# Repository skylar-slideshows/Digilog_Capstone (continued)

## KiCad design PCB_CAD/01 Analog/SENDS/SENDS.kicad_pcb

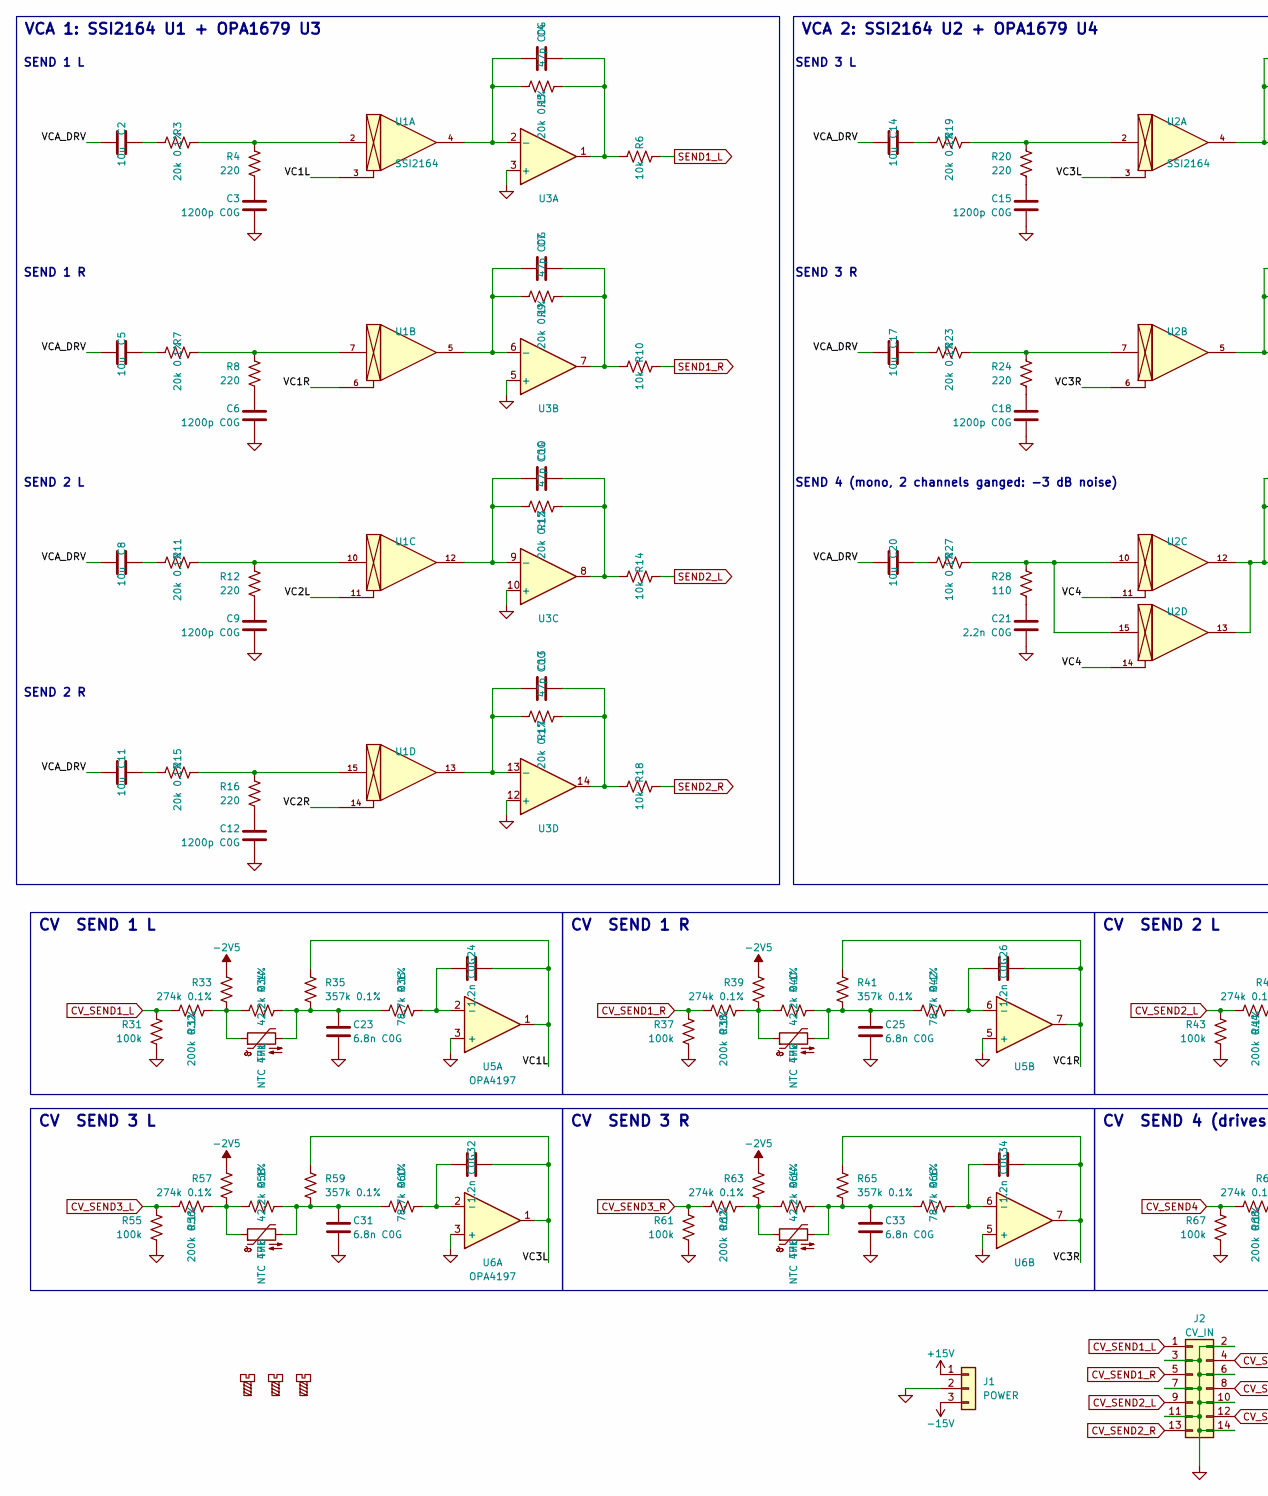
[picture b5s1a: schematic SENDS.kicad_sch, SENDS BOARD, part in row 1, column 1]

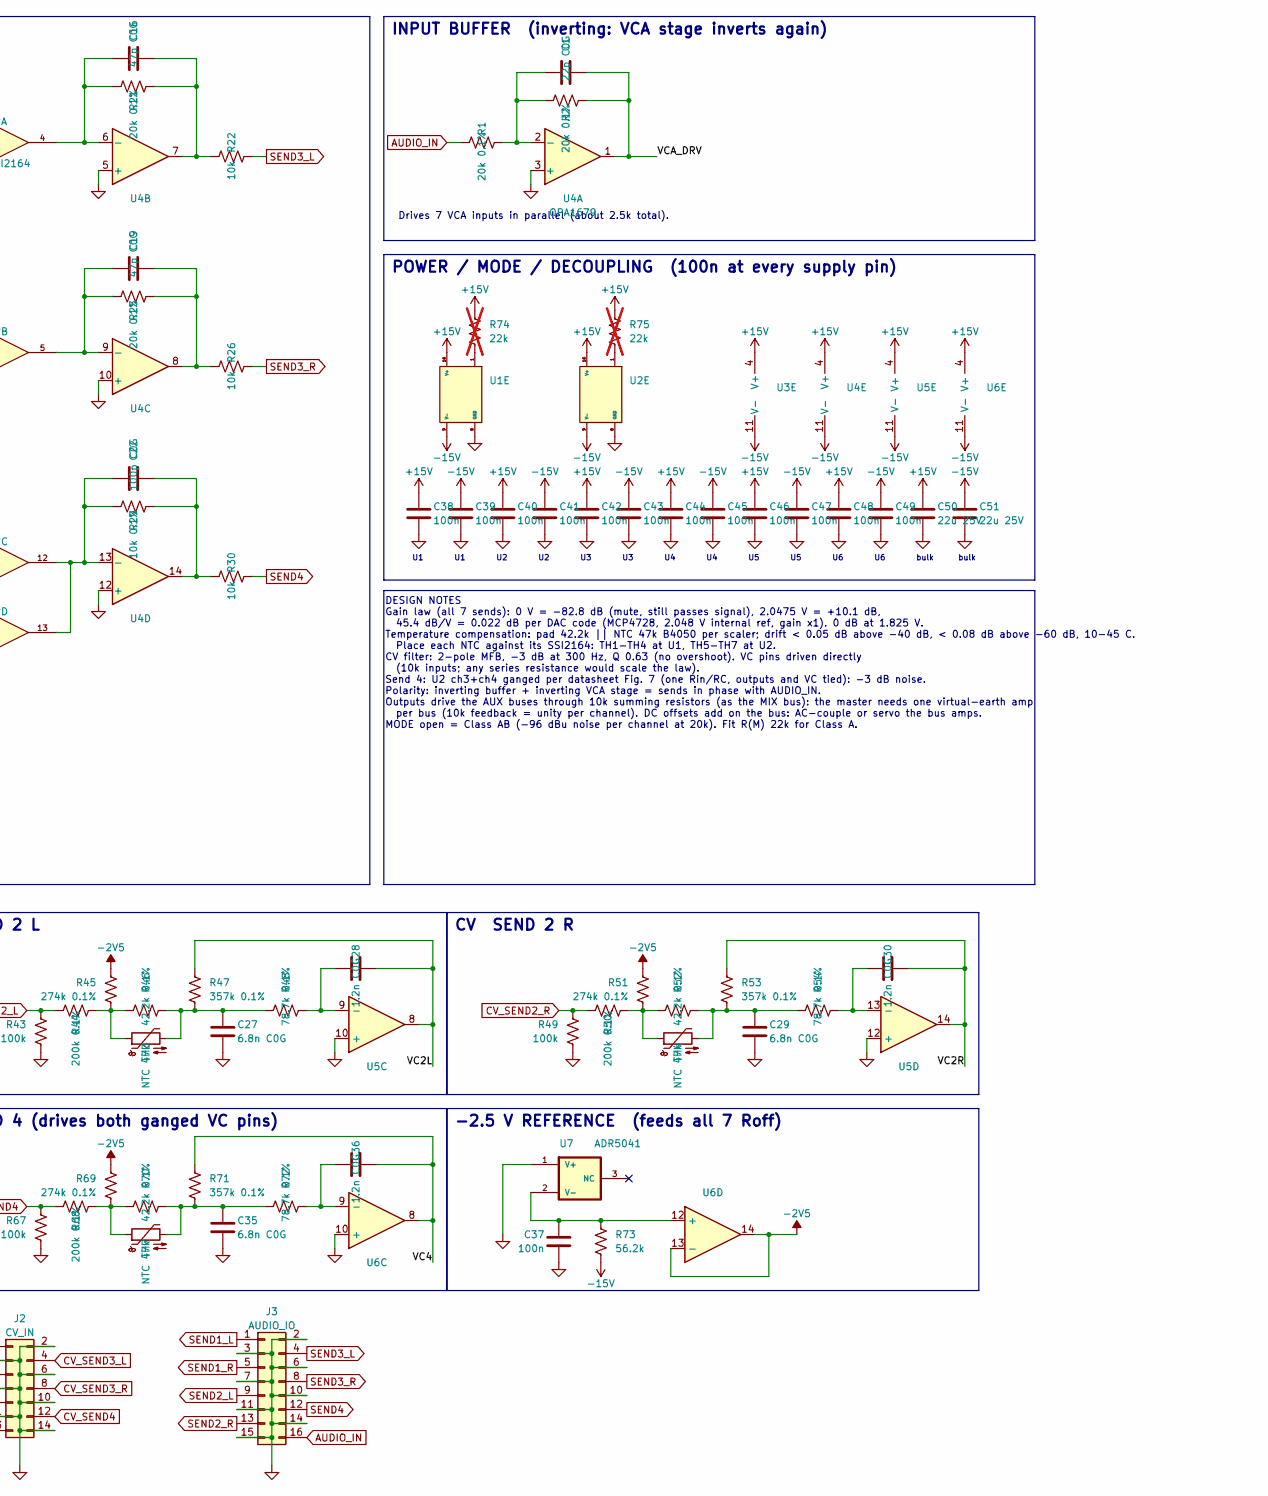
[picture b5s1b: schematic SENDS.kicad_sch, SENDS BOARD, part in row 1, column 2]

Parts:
C1: 22p C0G; C_0603_1608Metric; LCSC C105620
C2, C5, C8, C11, C14, C17, C20: 10u; CP_Elec_6.3x5.4_Nichicon; LCSC C192559
C3, C6, C9, C12, C15, C18: 1200p C0G; C_0603_1608Metric; LCSC C576796
C4, C7, C10, C13, C16, C19: 47p C0G; C_0603_1608Metric; LCSC C105622
C21: 2.2n C0G; C_0603_1608Metric; LCSC C107043
C22: 100p C0G; C_0603_1608Metric; LCSC C14665
C23, C25, C27, C29, C31, C33, C35: 6.8n C0G; C_0603_1608Metric; LCSC C513559
C24, C26, C28, C30, C32, C34, C36: 1.2n C0G; C_0603_1608Metric; LCSC C576796
C37, C38, C39, C40, C41, C42, C43, C44, C45, C46, C47, C48, C49: 100n; C_0603_1608Metric; LCSC C1590
C50, C51: 22u 25V; C_1210_3225Metric; LCSC C21397
H1, H2, H3: MountingScrew; MountingHole_2.2mm_M2; LCSC dnp
J1: POWER; PinHeader_1x03_P2.54mm_Vertical; LCSC dnp
J2: CV_IN; PinHeader_2x07_P2.54mm_Vertical; LCSC dnp
J3: AUDIO_IO; PinHeader_2x08_P2.54mm_Vertical; LCSC dnp
R1, R2, R3, R5, R7, R9, R11, R13, R15, R17, R19, R21, R23, R25: 20k 0.1%; R_0603_1608Metric; LCSC C190611
R4, R8, R12, R16, R20, R24: 220; R_0603_1608Metric; LCSC C217883
R6, R10, R14, R18, R22, R26, R30: 10k; R_0603_1608Metric; LCSC C95204
R27, R29: 10k 0.1%; R_0603_1608Metric; LCSC C95204
R28: 110; R_0603_1608Metric; LCSC C351689
R31, R37, R43, R49, R55, R61, R67: 100k; R_0603_1608Metric; LCSC C122538
R32, R38, R44, R50, R56, R62, R68: 200k 0.1%; R_0603_1608Metric; LCSC C136955
R33, R39, R45, R51, R57, R63, R69: 274k 0.1%; R_0603_1608Metric; LCSC C311972
R34, R40, R46, R52, R58, R64, R70: 42.2k 0.1%; R_0603_1608Metric; LCSC C861398
R35, R41, R47, R53, R59, R65, R71: 357k 0.1%; R_0603_1608Metric; LCSC C217978
R36, R42, R48, R54, R60, R66, R72: 78.7k 0.1%; R_0603_1608Metric; LCSC C861558
R73: 56.2k; R_0603_1608Metric; LCSC C23080
R74, R75: 22k; R_0603_1608Metric; LCSC C23344; not fitted
TH1, TH2, TH3, TH4, TH5, TH6, TH7: NTC 47k; R_Axial_DIN0207_L6.3mm_D2.5mm_P2.54mm_Vertical; LCSC dnp
U1, U2: SSI2164; SSI2164_breakout; LCSC dnp
U3, U4: OPA1679; TSSOP-14_4.4x5mm_P0.65mm; LCSC C2057264
U5, U6: OPA4197; SOIC-14_3.9x8.7mm_P1.27mm; LCSC C2058532
U7: ADR5041; SOT-23; LCSC C2686108

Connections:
+15V: C38.1, C40.1, C42.1, C44.1, C46.1, C48.1, C50.1, J1.1, R74.1, R75.1, U1.16 (V+), U2.16 (V+), U3.4 (V+), U4.4 (V+), U5.4 (V+), U6.4 (V+)
-2V5: R33.1, R39.1, R45.1, R51.1, R57.1, R63.1, R69.1, U6.13 (-), U6.14
-15V: C39.1, C41.1, C43.1, C45.1, C47.1, C49.1, C51.1, J1.3, R73.2, U1.9 (V-), U2.9 (V-), U3.11 (V-), U4.11 (V-), U5.11 (V-), U6.11 (V-)
/VC1L: C24.2, R35.1, U1.3, U5.1
/VC1R: C26.2, R41.1, U1.6, U5.7
/VC2L: C28.2, R47.1, U1.11, U5.8
/VC2R: C30.2, R53.1, U1.14, U5.14
/VC3L: C32.2, R59.1, U2.3, U6.1
/VC3R: C34.2, R65.1, U2.6, U6.7
/VC4: C36.2, R71.1, U2.11, U2.14, U6.8
/VCA_DRV: C1.2, C2.1, C5.1, C8.1, C11.1, C14.1, C17.1, C20.1, R2.2, U4.1
AUDIO_IN: J3.16, R1.1
CV_SEND1_L: J2.1, R31.1, R32.1
CV_SEND1_R: J2.5, R37.1, R38.1
CV_SEND2_L: J2.9, R43.1, R44.1
CV_SEND2_R: J2.13, R49.1, R50.1
CV_SEND3_L: J2.4, R55.1, R56.1
CV_SEND3_R: J2.8, R61.1, R62.1
CV_SEND4: J2.12, R67.1, R68.1
GND: C3.2, C6.2, C9.2, C12.2, C15.2, C18.2, C21.2, C23.2, C25.2, C27.2, C29.2, C31.2, C33.2, C35.2, C37.2, C38.2, C39.2, C40.2, C41.2, C42.2, C43.2, C44.2, C45.2, C46.2, C47.2, C48.2, C49.2, C50.2, C51.2, J1.2, J2.2, J2.3, J2.6, J2.7, J2.10, J2.11, J2.14, J3.2, J3.3, J3.6, J3.7, J3.10, J3.11, J3.14, J3.15, R31.2, R37.2, R43.2, R49.2, R55.2, R61.2, R67.2, U1.8 (GND), U2.8 (GND), U3.3 (+), U3.5 (+), U3.10 (+), U3.12 (+), U4.3 (+), U4.5 (+), U4.10 (+), U4.12 (+), U5.3 (+), U5.5 (+), U5.10 (+), U5.12 (+), U6.3 (+), U6.5 (+), U6.10 (+), U7.1 (V+)
unnamed: C2.2, R3.1
unnamed: C3.1, R4.2
unnamed: C4.2, R5.2, R6.1, U3.1
unnamed: C5.2, R7.1
unnamed: C6.1, R8.2
unnamed: C7.2, R9.2, R10.1, U3.7
unnamed: C8.2, R11.1
unnamed: C9.1, R12.2
unnamed: C10.2, R13.2, R14.1, U3.8
unnamed: C11.2, R15.1
unnamed: C12.1, R16.2
unnamed: C13.2, R17.2, R18.1, U3.14
unnamed: C14.2, R19.1
unnamed: C15.1, R20.2
unnamed: C16.2, R21.2, R22.1, U4.7
unnamed: C17.2, R23.1
unnamed: C18.1, R24.2
unnamed: C19.2, R25.2, R26.1, U4.8
unnamed: C20.2, R27.1
unnamed: C21.1, R28.2
unnamed: C22.2, R29.2, R30.1, U4.14
unnamed: C23.1, R34.2, R35.2, R36.1, TH1.2
unnamed: C25.1, R40.2, R41.2, R42.1, TH2.2
unnamed: C27.1, R46.2, R47.2, R48.1, TH3.2
unnamed: C29.1, R52.2, R53.2, R54.1, TH4.2
unnamed: C31.1, R58.2, R59.2, R60.1, TH5.2
unnamed: C33.1, R64.2, R65.2, R66.1, TH6.2
unnamed: C35.1, R70.2, R71.2, R72.1, TH7.2
unnamed: R3.2, R4.1, U1.2
unnamed: R7.2, R8.1, U1.7
unnamed: R11.2, R12.1, U1.10
unnamed: R15.2, R16.1, U1.15
unnamed: R19.2, R20.1, U2.2
unnamed: R23.2, R24.1, U2.7
unnamed: R27.2, R28.1, U2.10, U2.15
unnamed: R32.2, R33.2, R34.1, TH1.1
unnamed: R38.2, R39.2, R40.1, TH2.1
unnamed: R44.2, R45.2, R46.1, TH3.1
unnamed: R50.2, R51.2, R52.1, TH4.1
unnamed: R56.2, R57.2, R58.1, TH5.1
unnamed: R62.2, R63.2, R64.1, TH6.1
unnamed: R68.2, R69.2, R70.1, TH7.1
unnamed: R74.2, U1.1
unnamed: R75.2, U2.1
unnamed: C4.1, R5.1, U1.4, U3.2 (-)
unnamed: C7.1, R9.1, U1.5, U3.6 (-)
unnamed: C10.1, R13.1, U1.12, U3.9 (-)
unnamed: C13.1, R17.1, U1.13, U3.13 (-)
unnamed: C1.1, R1.2, R2.1, U4.2 (-)
unnamed: C16.1, R21.1, U2.4, U4.6 (-)
unnamed: C19.1, R25.1, U2.5, U4.9 (-)
unnamed: C22.1, R29.1, U2.12, U2.13, U4.13 (-)
unnamed: C24.1, R36.2, U5.2 (-)
unnamed: C26.1, R42.2, U5.6 (-)
unnamed: C28.1, R48.2, U5.9 (-)
unnamed: C30.1, R54.2, U5.13 (-)
unnamed: C32.1, R60.2, U6.2 (-)
unnamed: C34.1, R66.2, U6.6 (-)
unnamed: C36.1, R72.2, U6.9 (-)
unnamed: C37.1, R73.1, U6.12 (+), U7.2 (V-)
SEND1_L: J3.1, R6.2
SEND1_R: J3.5, R10.2
SEND2_L: J3.9, R14.2
SEND2_R: J3.13, R18.2
SEND3_L: J3.4, R22.2
SEND3_R: J3.8, R26.2
SEND4: J3.12, R30.2

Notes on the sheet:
bulk
SEND 2 R
SEND 1 L
CV SEND 4 (drives both ganged VC pins)
SEND 1 R
DESIGN NOTES Gain law (all 7 sends): 0 V = -82.8 dB (mute, still passes signal), 2.0475 V = +10.1 dB, 45.4 dB/V = 0.022 dB per DAC code (MCP4728, 2.048 V internal ref, gain x1). 0 dB at 1.825 V. Temperature compensation: pad 42.2k || NTC 47k B4050 per scaler; drift < 0.05 dB above -40 dB, < 0.08 dB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
VCA 1: SSI2164 U1 + OPA1679 U3
CV SEND 1 R
Drives 7 VCA inputs in parallel (about 2.5k total).
-2.5 V REFERENCE (feeds all 7 Roff)
CV SEND 3 R
VCA 2: SSI2164 U2 + OPA1679 U4
SEND 4 (mono, 2 channels ganged: -3 dB noise)
SEND 2 L
CV SEND 1 L
SEND 3 L
CV SEND 2 L
INPUT BUFFER (inverting: VCA stage inverts again)
CV SEND 2 R
SEND 3 R
POWER / MODE / DECOUPLING (100n at every supply pin)
CV SEND 3 L

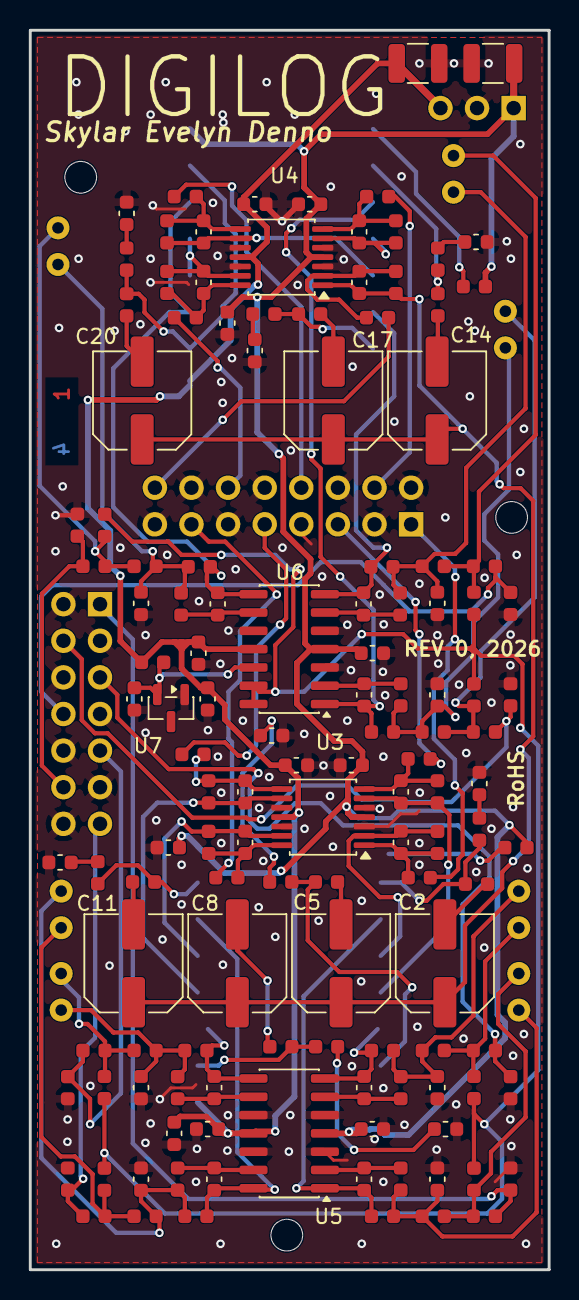
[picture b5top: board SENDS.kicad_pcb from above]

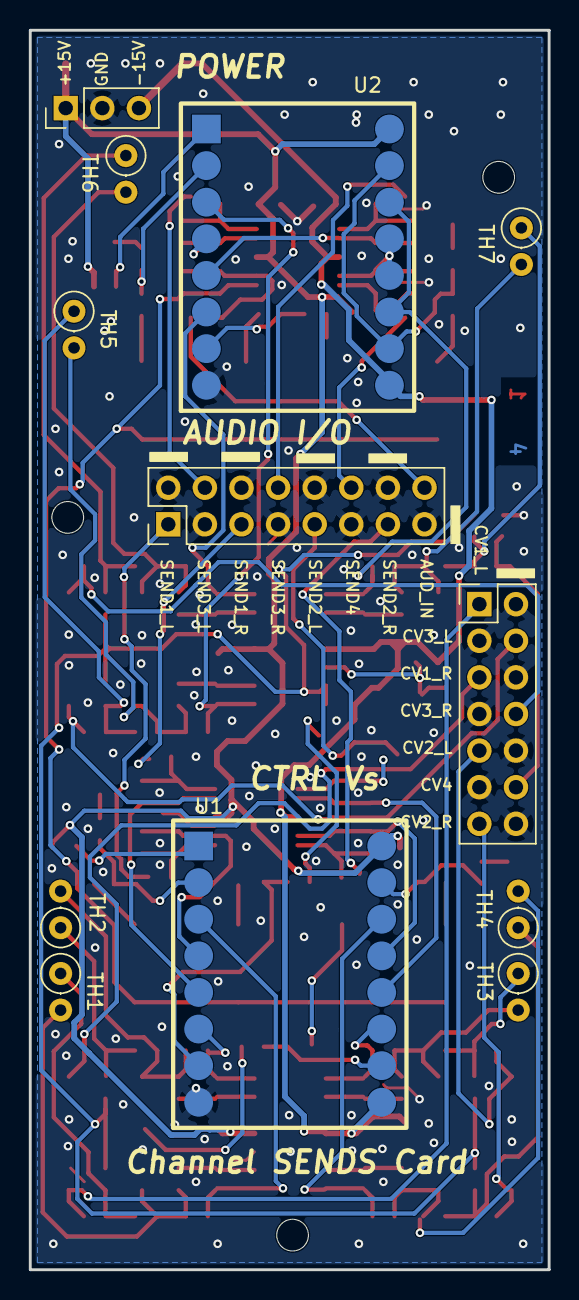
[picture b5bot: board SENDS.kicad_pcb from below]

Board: 4 copper layers, 36.0 x 86.0 mm, 146 parts (12 on the bottom side), 87 nets.

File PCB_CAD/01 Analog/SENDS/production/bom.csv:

Designator,Footprint,Quantity,Value,LCSC Part #
C1,0603,1,22p C0G,C105620
"C10, C13, C16, C19, C4, C7",0603,6,47p C0G,C105622
"C11, C14, C17, C2, C20, C5, C8",CP_Elec_6.3x5.4_Nichicon,7,10u,C192559
"C12, C15, C18, C3, C6, C9",0603,6,1200p C0G,C576796
C21,0603,1,2.2n C0G,C107043
C22,0603,1,100p C0G,C14665
"C23, C25, C27, C29, C31, C33, C35",0603,7,6.8n C0G,C513559
"C24, C26, C28, C30, C32, C34, C36",0603,7,1.2n C0G,C576796
"C37, C38, C39, C40, C41, C42, C43, C44, C45, C46, C47, C48, C49",0603,13,100n,C1590
"C50, C51",1210,2,22u 25V,C21397
J1,PinHeader_1x03_P2.54mm_Vertical,1,POWER,dnp
J2,PinHeader_2x07_P2.54mm_Vertical,1,CV_IN,dnp
J3,PinHeader_2x08_P2.54mm_Vertical,1,AUDIO_IO,dnp
"R1, R11, R13, R15, R17, R19, R2, R21, R23, R25, R3, R5, R7, R9",0603,14,20k 0.1%,C190611
"R10, R14, R18, R22, R26, R30, R6",0603,7,10k,C95204
"R12, R16, R20, R24, R4, R8",0603,6,220,C217883
"R27, R29",0603,2,10k 0.1%,C95204
R28,0603,1,110,C351689
"R31, R37, R43, R49, R55, R61, R67",0603,7,100k,C122538
"R32, R38, R44, R50, R56, R62, R68",0603,7,200k 0.1%,C136955
"R33, R39, R45, R51, R57, R63, R69",0603,7,274k 0.1%,C311972
"R34, R40, R46, R52, R58, R64, R70",0603,7,42.2k 0.1%,C861398
"R35, R41, R47, R53, R59, R65, R71",0603,7,357k 0.1%,C217978
"R36, R42, R48, R54, R60, R66, R72",0603,7,78.7k 0.1%,C861558
R73,0603,1,56.2k,C23080
"R74, R75",0603,2,22k,C23344
"TH1, TH2, TH3, TH4, TH5, TH6, TH7",R_Axial_DIN0207_L6.3mm_D2.5mm_P2.54mm_Vertical,7,NTC 47k,dnp
"U1, U2",SSI2164_breakout,2,SSI2164,dnp
"U3, U4",TSSOP-14_4.4x5mm_P0.65mm,2,OPA1679,C2057264
"U5, U6",SOIC-14_3.9x8.7mm_P1.27mm,2,OPA4197,C2058532
U7,SOT-23,1,ADR5041,C2686108

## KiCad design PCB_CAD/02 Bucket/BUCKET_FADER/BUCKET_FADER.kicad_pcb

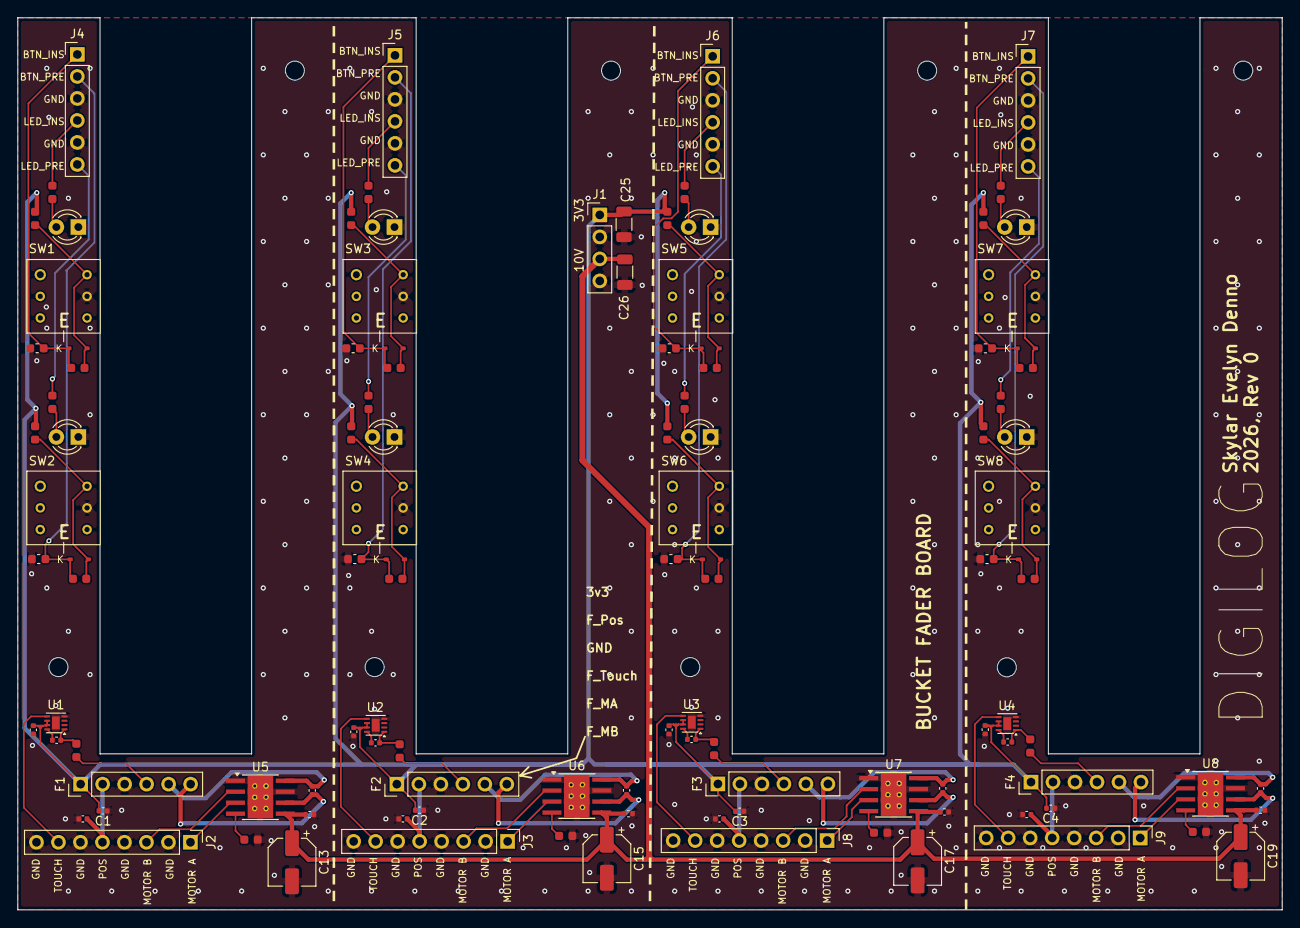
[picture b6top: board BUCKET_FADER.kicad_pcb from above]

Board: 4 copper layers, 146.0 x 103.0 mm, 123 parts (0 on the bottom side), 75 nets.

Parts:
C1, C2, C3, C4, C5, C6, C7, C8, C14, C16, C18, C20, C35, C36, C37, C38: 100n; C_0402_1005Metric
C9, C10, C11, C12, C21, C22, C23, C24: 10n; C_0402_1005Metric
C13, C15, C17, C19: 22u; CP_Elec_5x5.4
C25, C26: 10u; C_1206_3216Metric
C27, C28, C29, C30, C31, C32, C33, C34: 1u; C_0603_1608Metric
D1, D2, D3, D4, D9, D10, D11, D12: 1N4148; D_SOD-323
D5, D6, D7, D8, D13, D14, D15, D16: LED; LED_D3.0mm_FlatTop
F1, F2, F3, F4: Alps_RSA0N11M9; PinHeader_1x06_P2.54mm_Vertical
H1, H2, H3, H4, H5, H6, H7, H8: MountingScrew; MountingHole_2.2mm_M2
J1: POW; PinHeader_1x04_P2.54mm_Vertical
J2: F0_MCU; PinHeader_1x08_P2.54mm_Vertical
J3: F1_MCU; PinHeader_1x08_P2.54mm_Vertical
J4: F0_BTN; PinHeader_1x06_P2.54mm_Vertical
J5: F1_BTN; PinHeader_1x06_P2.54mm_Vertical
J6: F2_BTN; PinHeader_1x06_P2.54mm_Vertical
J7: F3_BTN; PinHeader_1x06_P2.54mm_Vertical
J8: F2_MCU; PinHeader_1x08_P2.54mm_Vertical
J9: F3_MCU; PinHeader_1x08_P2.54mm_Vertical
R1, R2, R3, R4: 10k; R_0603_1608Metric
R5, R6, R7, R8: 82k; R_0603_1608Metric
R9, R10, R11, R12, R21, R22, R23, R24: 47k; R_0603_1608Metric
R13, R14, R15, R16, R25, R26, R27, R28: 15k; R_0603_1608Metric
R17, R18, R19, R20, R29, R30, R31, R32: 6.8k; R_0603_1608Metric
SW1, SW3, SW5, SW7: C0_B10; TL2201EEZB
SW2, SW4, SW6, SW8: C0_B11; TL2201EEZB
U1, U2, U3, U4: AT42QT1011-M; DFN-8-1EP_2x2mm_P0.5mm_EP0.9x1.5mm
U5, U6, U7, U8: DRV8871DDA; Texas_HTSOP-8-1EP_3.9x4.9mm_P1.27mm_EP2.95x4.9mm_Mask2.4x3.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

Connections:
+3V3: C1.2, C2.2, C3.2, C4.2, C5.2, C6.2, C7.2, C8.2, C25.1, F1.1, F2.1, F3.1, F4.1, J1.1, R9.1, R10.1, R11.1, R12.1, R21.1, R22.1, R23.1, R24.1, U1.6 (SYNC), U1.7 (VDD), U2.6 (SYNC), U2.7 (VDD), U3.6 (SYNC), U3.7 (VDD), U4.6 (SYNC), U4.7 (VDD)
+10V: C13.1, C14.2, C15.1, C16.2, C17.1, C18.2, C19.1, C20.2, C26.1, J1.3, U5.5 (VM), U6.5 (VM), U7.5 (VM), U8.5 (VM)
/F0_MotA: C21.1, F1.5 (A), U5.8 (OUT2)
/F0_MotB: C21.2, F1.6 (B), U5.6 (OUT1)
/F0_Touch: F1.4 (T), R1.2
/F1_MotA: C22.1, F2.5 (A), U6.8 (OUT2)
/F1_MotB: C22.2, F2.6 (B), U6.6 (OUT1)
/F1_Touch: F2.4 (T), R2.2
/F2_MotA: C23.1, F3.5 (A), U7.8 (OUT2)
/F2_MotB: C23.2, F3.6 (B), U7.6 (OUT1)
/F2_Touch: F3.4 (T), R3.2
/F3_MotA: C24.1, F4.5 (A), U8.8 (OUT2)
/F3_MotB: C24.2, F4.6 (B), U8.6 (OUT1)
/F3_Touch: F4.4 (T), R4.2
F0_BTN_INS: C27.1, D1.1 (K), J4.1, R13.2
F0_BTN_PRE: C28.1, D2.1 (K), J4.2, R14.2
F0_LED_INS: J4.4, R17.2
F0_LED_PRE: J4.6, R18.2
F0_MA: J2.1, U5.3 (IN1)
F0_MB: J2.3, U5.2 (IN2)
F0_POS: C35.2, F1.2, J2.5
F0_TOUCH: J2.7, U1.5 (OUT)
F1_BTN_INS: C29.1, D3.1 (K), J5.1, R15.2
F1_BTN_PRE: C30.1, D4.1 (K), J5.2, R16.2
F1_LED_INS: J5.4, R19.2
F1_LED_PRE: J5.6, R20.2
F1_MA: J3.1, U6.3 (IN1)
F1_MB: J3.3, U6.2 (IN2)
F1_POS: C36.2, F2.2, J3.5
F1_TOUCH: J3.7, U2.5 (OUT)
F2_BTN_INS: C31.1, D9.1 (K), J6.1, R25.2
F2_BTN_PRE: C32.1, D10.1 (K), J6.2, R26.2
F2_LED_INS: J6.4, R29.2
F2_LED_PRE: J6.6, R30.2
F2_MA: J8.1, U7.3 (IN1)
F2_MB: J8.3, U7.2 (IN2)
F2_POS: C37.2, F3.2, J8.5
F2_TOUCH: J8.7, U3.5 (OUT)
F3_BTN_INS: C33.1, D11.1 (K), J7.1, R27.2
F3_BTN_PRE: C34.1, D12.1 (K), J7.2, R28.2
F3_LED_INS: J7.4, R31.2
F3_LED_PRE: J7.6, R32.2
F3_MA: J9.1, U8.3 (IN1)
F3_MB: J9.3, U8.2 (IN2)
F3_POS: C38.2, F4.2, J9.5
F3_TOUCH: J9.7, U4.5 (OUT)
GND: C1.1, C2.1, C3.1, C4.1, C5.1, C6.1, C7.1, C8.1, C13.2, C14.1, C15.2, C16.1, C17.2, C18.1, C19.2, C20.1, C25.2, C26.2, C27.2, C28.2, C29.2, C30.2, C31.2, C32.2, C33.2, C34.2, C35.1, C36.1, C37.1, C38.1, D5.1 (K), D6.1 (K), D7.1 (K), D8.1 (K), D13.1 (K), D14.1 (K), D15.1 (K), D16.1 (K), F1.3, F2.3, F3.3, F4.3, J1.2, J1.4, J2.2, J2.4, J2.6, J2.8, J3.2, J3.4, J3.6, J3.8, J4.3, J4.5, J5.3, J5.5, J6.3, J6.5, J7.3, J7.5, J8.2, J8.4, J8.6, J8.8, J9.2, J9.4, J9.6, J9.8, R5.2, R6.2, R7.2, R8.2, SW1.2 (B), SW2.2 (B), SW3.2 (B), SW4.2 (B), SW5.2 (B), SW6.2 (B), SW7.2 (B), SW8.2 (B), U1.4 (VSS), U1.9 (VSS), U2.4 (VSS), U2.9 (VSS), U3.4 (VSS), U3.9 (VSS), U4.4 (VSS), U4.9 (VSS), U5.1 (GND), U5.7 (GND), U5.9 (GND), U6.1 (GND), U6.7 (GND), U6.9 (GND), U7.1 (GND), U7.7 (GND), U7.9 (GND), U8.1 (GND), U8.7 (GND), U8.9 (GND)
unnamed: D1.2 (A), R9.2, R13.1, SW1.3 (C)
unnamed: D2.2 (A), R10.2, R14.1, SW2.3 (C)
unnamed: D3.2 (A), R11.2, R15.1, SW3.3 (C)
unnamed: D4.2 (A), R12.2, R16.1, SW4.3 (C)
unnamed: D5.2 (A), R17.1
unnamed: D6.2 (A), R18.1
unnamed: D7.2 (A), R19.1
unnamed: D8.2 (A), R20.1
unnamed: D9.2 (A), R21.2, R25.1, SW5.3 (C)
unnamed: D10.2 (A), R22.2, R26.1, SW6.3 (C)
unnamed: D11.2 (A), R23.2, R27.1, SW7.3 (C)
unnamed: D12.2 (A), R24.2, R28.1, SW8.3 (C)
unnamed: D13.2 (A), R29.1
unnamed: D14.2 (A), R30.1
unnamed: D15.2 (A), R31.1
unnamed: D16.2 (A), R32.1
unnamed: C9.2, U1.8 (SNS)
unnamed: C9.1, R1.1, U1.1 (SNSK)
unnamed: C10.2, U2.8 (SNS)
unnamed: C10.1, R2.1, U2.1 (SNSK)
unnamed: C11.2, U3.8 (SNS)
unnamed: C11.1, R3.1, U3.1 (SNSK)
unnamed: C12.2, U4.8 (SNS)
unnamed: C12.1, R4.1, U4.1 (SNSK)
unnamed: R5.1, U5.4 (ILIM)
unnamed: R6.1, U6.4 (ILIM)
unnamed: R7.1, U7.4 (ILIM)
unnamed: R8.1, U8.4 (ILIM)
